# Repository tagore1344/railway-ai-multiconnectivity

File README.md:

# AI Railway Multi-Connectivity Gateway

Simulation and machine-learning research prototype for reliable passenger Wi-Fi on high-mobility railway networks.

## Project progression

- V1: Multi-connectivity baseline
- V2: Capacity-aware load balancing
- V3: Automatic failover
- V4: Train mobility and changing link quality
- V5.1: Traffic measurement and time-series logging
- V6: Adaptive link monitoring and scoring
- V7: Multi-condition simulation dataset
- V8/V8.1: Machine-learning prediction baselines
- V8.2: Randomized conditions and unseen-seed future-network prediction
- V9: Reactive vs predictive policy evaluation
- V10: Multi-link bonding capacity-model stage
- V11: Predictive selection + bonding-capacity integration
- V12.2–V12.5: Packet-level striping, reordering, bounded buffering, and latency-aware bonding prototypes
- V13: Predictive path selection + bonding controller
- V14: Autonomous failover/recovery controller
- V15: Passenger-aware traffic allocation
- V16: Route/digital-twin prediction
- V17: Hardware gateway architecture

## Current validated evidence

- V7 dataset: 840 observations from 40 simulation conditions.
- V8.2: 99.24% next-network prediction accuracy on 132 observations from 12 unseen randomized seeds.
- V12.5 local ns-3 run: 61.7514 Mbps unique received goodput and 59.8382 Mbps in-order goodput with bonding enabled, compared with 28.966 Mbps and 27.0396 Mbps for the single-link baseline under the same 64 Mbps offered load.

These are simulation results from the project's synthetic ns-3 model. They do not establish real-world railway or cellular-network performance.

## Repository structure

```text
v11/                         Predictive + bonding integration
v12/                         Packet-level bonding experiments
v13/                         Predictive bonding controller
v14/                         Failover/recovery controller
v15/                         Passenger-aware traffic policy
v16/                         Route digital twin
v17/                         Hardware gateway specification
v9_predictive_vs_reactive.py Offline V9 policy evaluator
v10_bonding_emulation.py      V10 capacity/packet model
train_v81.py                  V8.1 predictor
train_v82.py                  V8.2 unseen-seed predictor
railway-v7-dataset.csv        V7 dataset
railway-v8.2-dataset.csv      Randomized V8.2 dataset
```

## Research roadmap

```text
adaptive monitoring
  -> future-link prediction
  -> predictive bonding
  -> failover/recovery
  -> passenger-aware policy
  -> route/digital-twin prediction
  -> packet-level bonding
  -> hardware gateway
  -> real-world multi-WAN/railway validation
```

## Validation boundary

No V13–V17 stage is considered experimentally validated until it is executed and its raw results are archived. Offline models and hardware designs must not be described as measured railway performance.

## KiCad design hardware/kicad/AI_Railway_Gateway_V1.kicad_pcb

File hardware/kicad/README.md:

# AI Railway Gateway V1 — KiCad Hardware Prototype

This is a first physical-interface PCB for the Raspberry Pi 5 railway multi-connectivity gateway.

## Architecture
- Raspberry Pi 5: 40-pin GPIO/control interface
- Three external modem/control headers
- GNSS UART/power header
- 5 V laboratory power input
- Input fuse and power indicator/decoupling
- Four M3 mounting-hole locations are planned in the next layout revision

## Important boundary
This is a laboratory prototype interface design, not a direct railway-power board. Do not connect it directly to train battery/traction power. Use an appropriate regulated 5 V bench supply during development.

The three cellular modems are intentionally external modules. The first prototype expects an external powered USB hub; a custom high-speed USB hub should be a later revision after the exact modem and hub IC are selected.

## Files
- `AI_Railway_Gateway_V1.kicad_pro`
- `AI_Railway_Gateway_V1.sch`
- `AI_Railway_Gateway_V1.kicad_pcb`

## Manufacturing gate
Do not fabricate this revision yet. First import/save the legacy schematic in KiCad 9, verify the exact connector/modem parts and pinouts, complete the net assignments, run ERC and PCB DRC, then generate Gerbers and drill files.

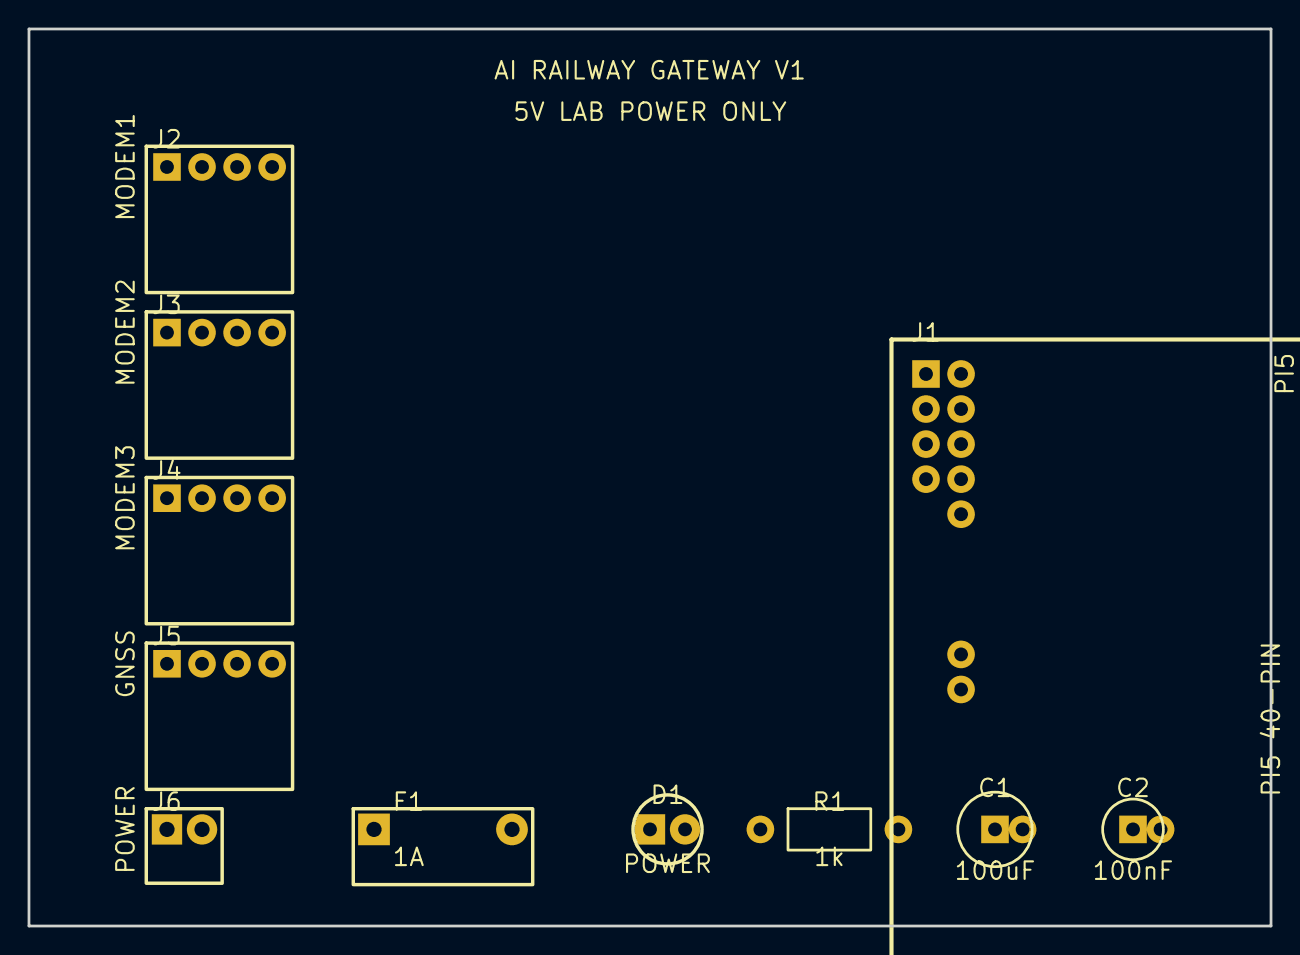
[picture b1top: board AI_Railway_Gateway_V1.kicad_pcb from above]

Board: 2 copper layers, 90.0 x 65.0 mm, 11 parts (0 on the bottom side), 2 nets, no tracks yet.

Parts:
C1: 100uF; C100u
C2: 100nF; C100n
D1: POWER; LED5mm
F1: 1A; Fuse
J1: RASPBERRY_PI_5_40PIN; Pi5_Header_2x20
J2: MODEM_1_CTRL; Header_1x04
J3: MODEM_2_CTRL; Header_1x04
J4: MODEM_3_CTRL; Header_1x04
J5: GNSS_UART; Header_1x04
J6: 5V_LAB_IN; Header_1x02
R1: 1k; R_Axial

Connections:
+5V: C1.1, C2.1, D1.1, F1.1, F1.2, J1.2, J1.4, J2.1, J3.1, J4.1, J5.1, J6.1, R1.1, R1.2
GND: C1.2, C2.2, D1.2, J1.6, J1.9, J1.20, J2.2, J3.2, J4.2, J5.2, J6.2
